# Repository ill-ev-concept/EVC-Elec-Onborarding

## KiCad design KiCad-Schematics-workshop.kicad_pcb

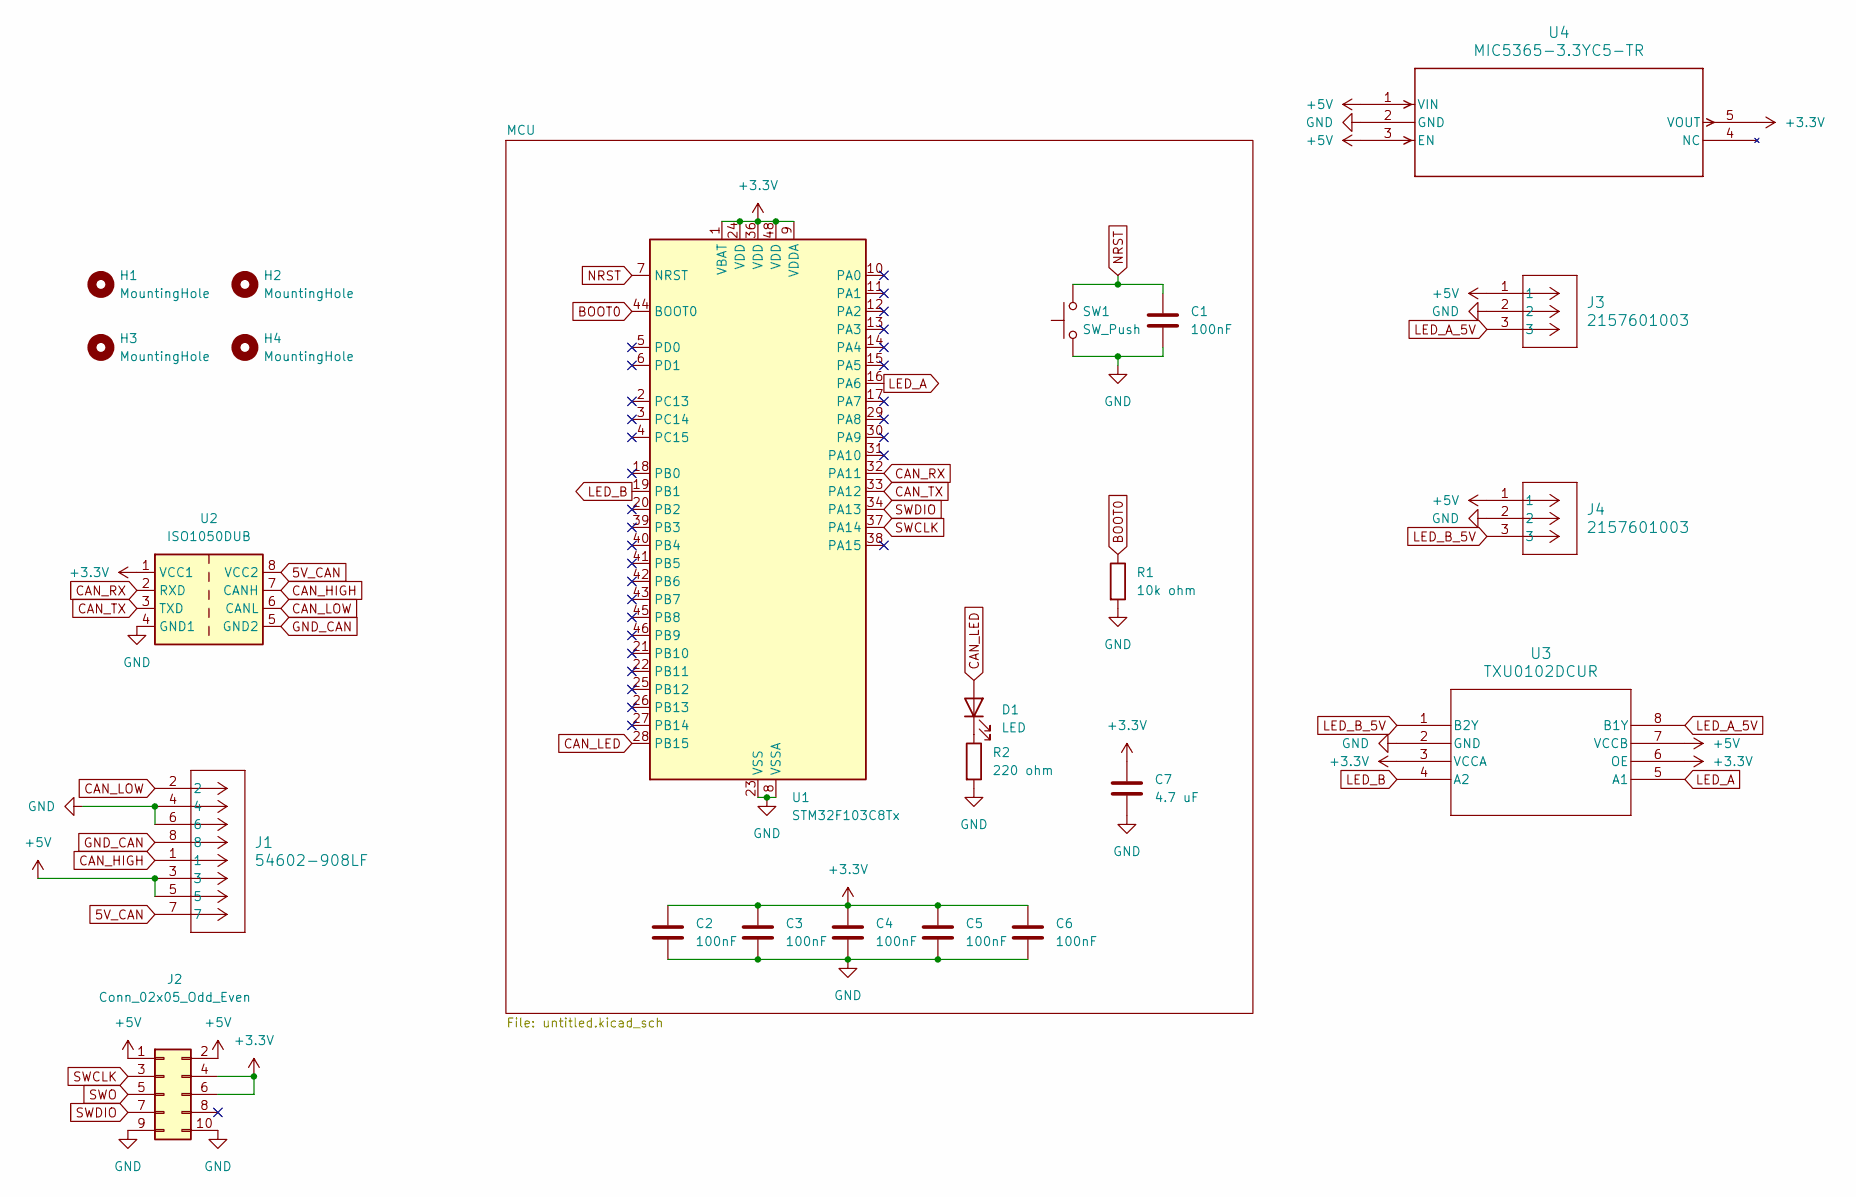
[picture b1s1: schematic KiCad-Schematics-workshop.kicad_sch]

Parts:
C1, C2, C3, C4, C5, C6: 100nF; C_0805_2012Metric
C7: 4.7 uF; C_0805_2012Metric
D1: LED; LED_0805_2012Metric
H1, H2, H3, H4: MountingHole; MountingHole_3.2mm_M3
J1: 54602-908LF; CONN8_2-908LF_AMP
J2: Conn_02x05_Odd_Even; PinHeader_2x05_P2.54mm_Horizontal
J3, J4: 2157601003; CONN_2157600003-SD_03_PEG_MOL
R1: 10k ohm; R_0805_2012Metric
R2: 220 ohm; R_0805_2012Metric
SW1: SW_Push; SW_SPST_EVQQ2
U1: STM32F103C8Tx; LQFP-48_7x7mm_P0.5mm
U2: ISO1050DUB; DUB0008A_L
U3: TXU0102DCUR; SOIC8_DCU_TEX
U4: MIC5365-3.3YC5-TR; SC-70_C5_MCH

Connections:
5V_CAN: J1.7, U2.8 (VCC2)
+3.3V: C2.1, C3.1, C4.1, C5.1, C6.1, C7.1, J2.4, J2.6, U1.1 (VBAT), U1.9 (VDDA), U1.24 (VDD), U1.36 (VDD), U1.48 (VDD), U2.1 (VCC1), U3.3 (VCCA), U3.6 (OE), U4.5 (VOUT)
+5V: J1.3, J1.5, J2.1, J2.2, J3.1, J4.1, U3.7 (VCCB), U4.1 (VIN), U4.3 (EN)
BOOT0: R1.1, U1.44 (BOOT0)
CAN_HIGH: J1.1, U2.7 (CANH)
CAN_LED: D1.2 (A), U1.28 (PB15)
CAN_LOW: J1.2, U2.6 (CANL)
CAN_RX: U1.32 (PA11), U2.2 (RXD)
CAN_TX: U1.33 (PA12), U2.3 (TXD)
GND: C1.2, C2.2, C3.2, C4.2, C5.2, C6.2, C7.2, J1.4, J1.6, J2.9, J2.10, J3.2, J4.2, R1.2, R2.2, SW1.1, U1.8 (VSSA), U1.23 (VSS), U1.35 (VSS), U1.47 (VSS), U2.4 (GND1), U3.2 (GND), U4.2 (GND)
GND_CAN: J1.8, U2.5 (GND2)
LED_A: U1.16 (PA6), U3.5 (A1)
LED_A_5V: J3.3, U3.8 (B1Y)
LED_B: U1.19 (PB1), U3.4 (A2)
LED_B_5V: J4.3, U3.1 (B2Y)
NRST: C1.1, SW1.2, U1.7 (NRST)
unnamed: D1.1 (K), R2.1
SWCLK: J2.3, U1.37 (PA14)
SWDIO: J2.7, U1.34 (PA13)
SWO: J2.5

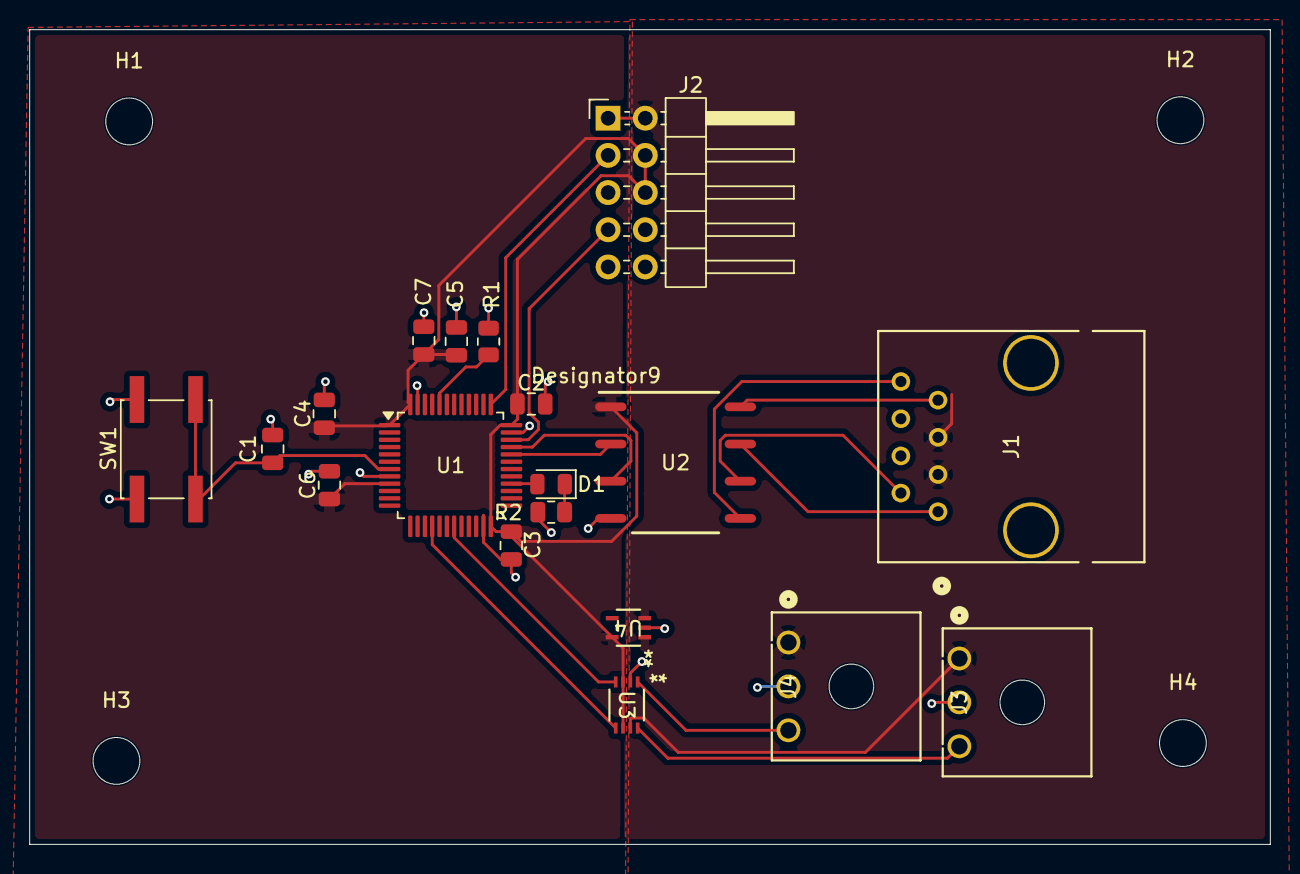
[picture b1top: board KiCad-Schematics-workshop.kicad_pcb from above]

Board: 2 copper layers, 84.8 x 55.7 mm, 23 parts (0 on the bottom side), 19 nets.

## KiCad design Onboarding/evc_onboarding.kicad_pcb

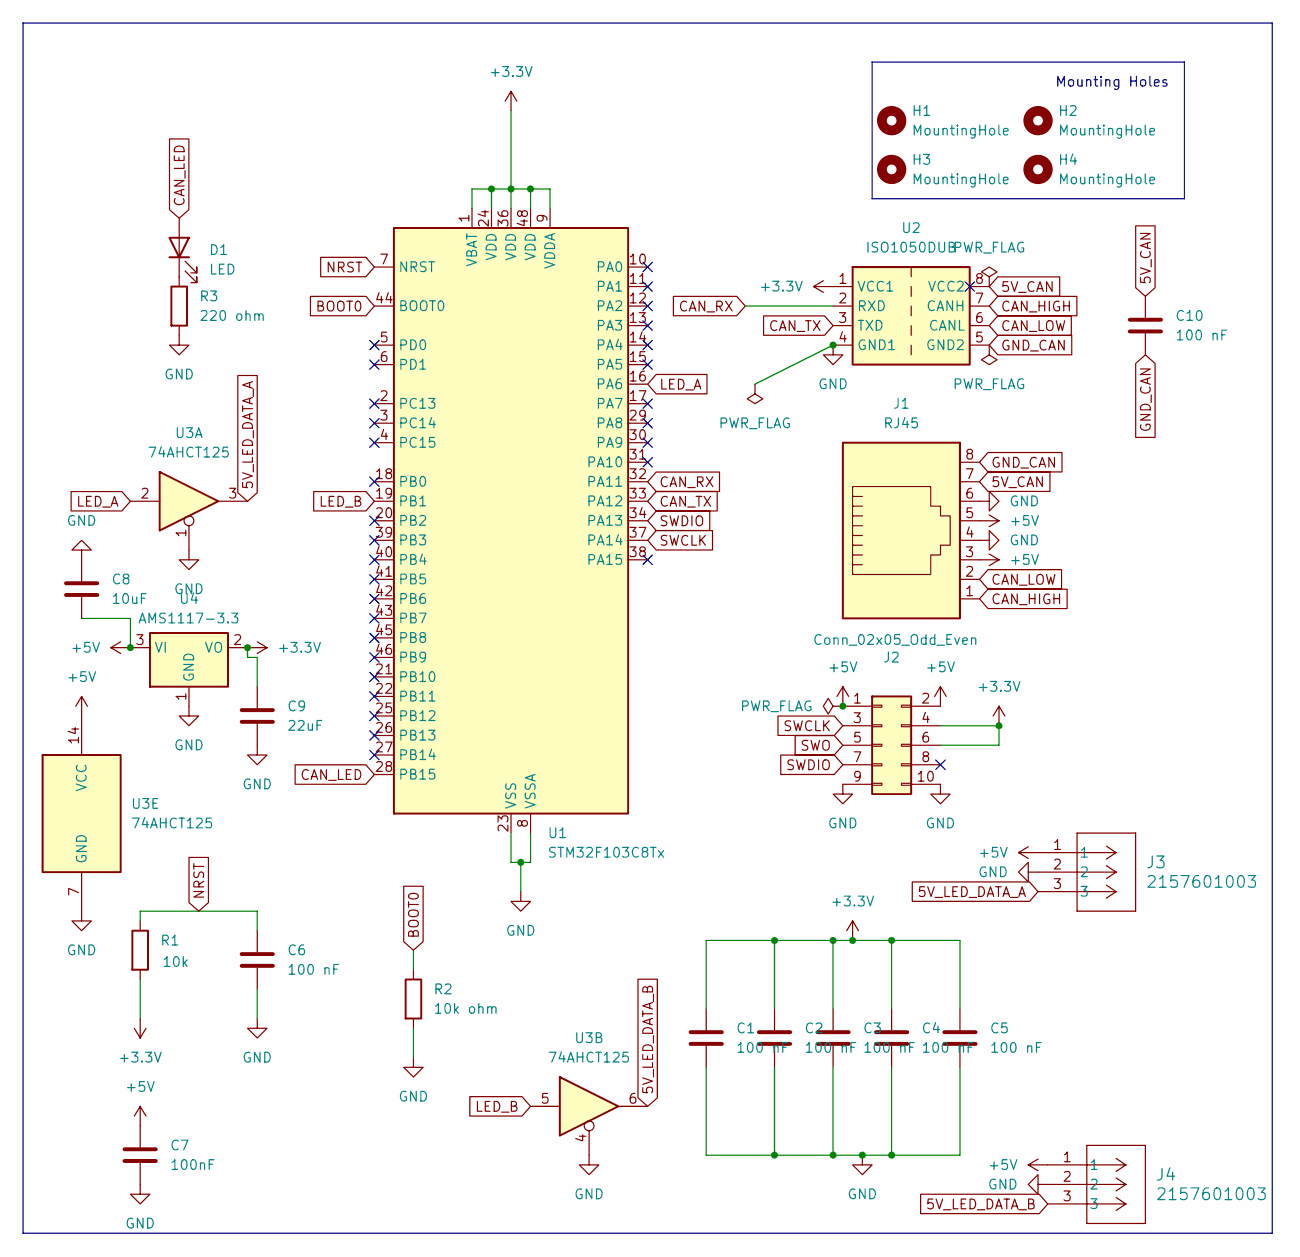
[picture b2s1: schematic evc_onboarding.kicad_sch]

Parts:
C1, C2, C3, C4, C5, C6, C10: 100 nF; C_0805_2012Metric
C7: 100nF; C_0805_2012Metric
C8: 10uF; C_1206_3216Metric
C9: 22uF; C_1206_3216Metric
D1: LED; LED_0805_2012Metric
H1, H2, H3, H4: MountingHole; MountingHole_4.3mm_M4
J1: RJ45; RJ45_Amphenol_RJMG1BD3B8K1ANR
J2: Conn_02x05_Odd_Even; PinHeader_2x05_P2.54mm_Vertical
J3, J4: 2157601003; CONN_2157600003-SD_03_PEG_MOL
R1: 10k; R_0805_2012Metric
R2: 10k ohm; R_0805_2012Metric
R3: 220 ohm; R_0805_2012Metric
U1: STM32F103C8Tx; LQFP-48_7x7mm_P0.5mm
U2: ISO1050DUB; SOP-8_6.62x9.15mm_P2.54mm
U3: 74AHCT125; SOIC-14_3.9x8.7mm_P1.27mm
U4: AMS1117-3.3; SOT-223-3_TabPin2

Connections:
5V_CAN: C10.1, J1.7, U2.8 (VCC2)
5V_LED_DATA_A: J3.3, U3.3
5V_LED_DATA_B: J4.3, U3.6
+3.3V: C1.1, C2.1, C3.1, C4.1, C5.1, C9.1, J2.4, J2.6, R1.2, U1.1 (VBAT), U1.9 (VDDA), U1.24 (VDD), U1.36 (VDD), U1.48 (VDD), U2.1 (VCC1), U4.2 (VO)
+5V: C7.1, C8.2, J1.3, J1.5, J2.1, J2.2, J3.1, J4.1, U3.14 (VCC), U4.3 (VI)
BOOT0: R2.1, U1.44 (BOOT0)
CAN_HIGH: J1.1, U2.7 (CANH)
CAN_LED: D1.2 (A), U1.28 (PB15)
CAN_LOW: J1.2, U2.6 (CANL)
CAN_RX: U1.32 (PA11), U2.2 (RXD)
CAN_TX: U1.33 (PA12), U2.3 (TXD)
GND: C1.2, C2.2, C3.2, C4.2, C5.2, C6.2, C7.2, C8.1, C9.2, J1.4, J1.6, J2.9, J2.10, J3.2, J4.2, R2.2, R3.2, U1.8 (VSSA), U1.23 (VSS), U1.35 (VSS), U1.47 (VSS), U2.4 (GND1), U3.1, U3.4, U3.7 (GND), U4.1 (GND)
GND_CAN: C10.2, J1.8, U2.5 (GND2)
LED_A: U1.16 (PA6), U3.2
LED_B: U1.19 (PB1), U3.5
NRST: C6.1, R1.1, U1.7 (NRST)
unnamed: D1.1 (K), R3.1
SWCLK: J2.3, U1.37 (PA14)
SWDIO: J2.7, U1.34 (PA13)
SWO: J2.5

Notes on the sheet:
Mounting Holes

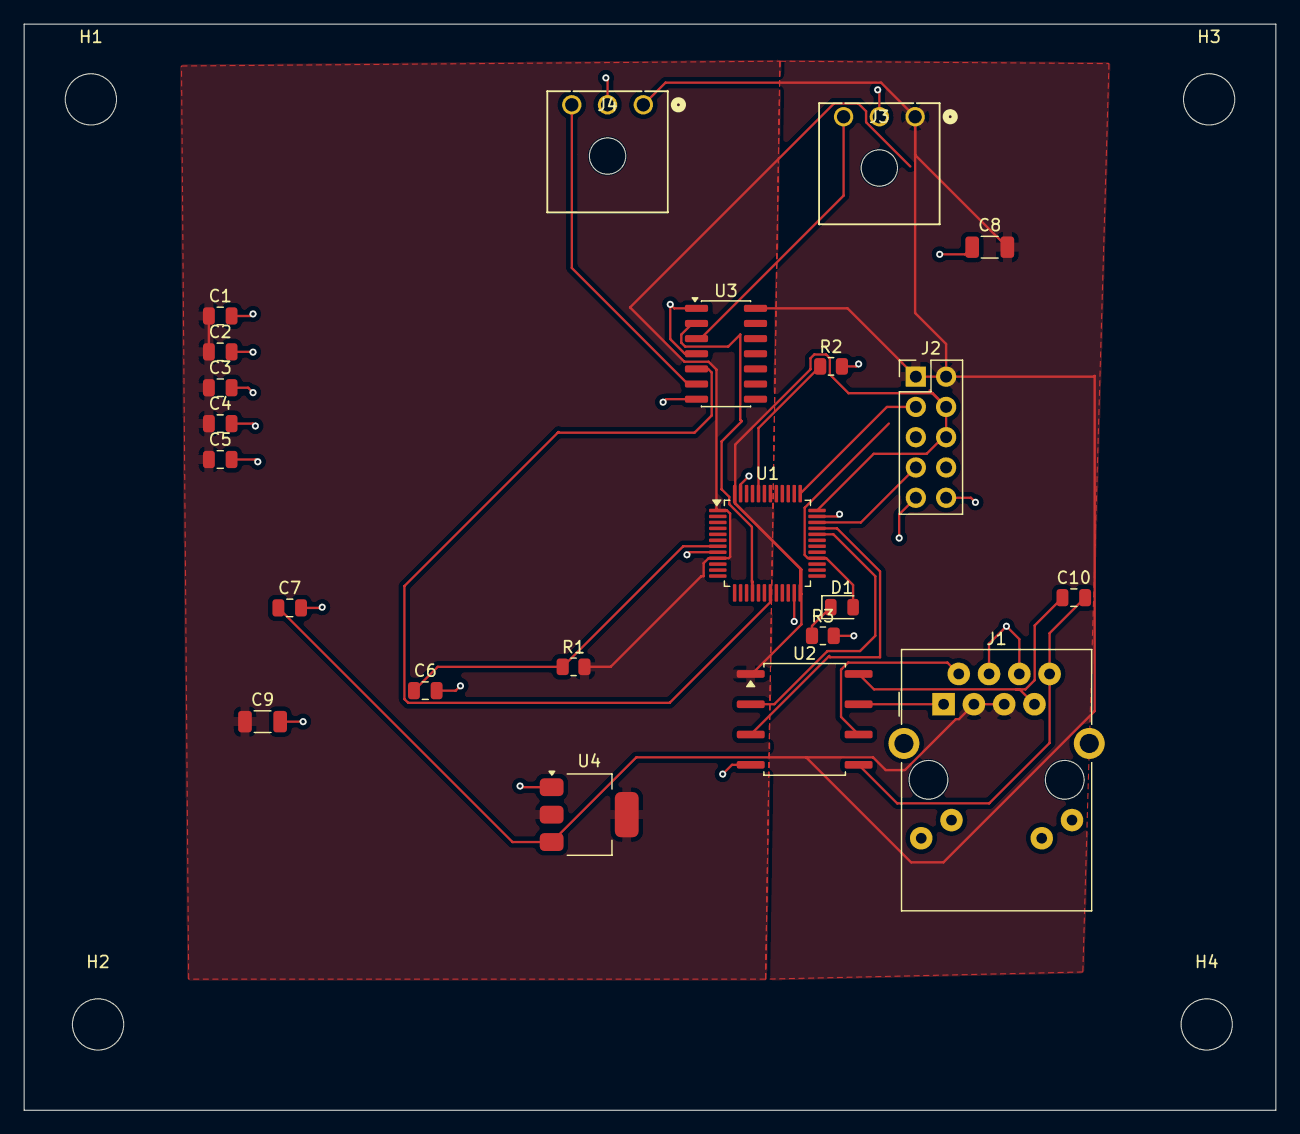
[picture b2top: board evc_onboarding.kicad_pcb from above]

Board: 2 copper layers, 105.0 x 91.1 mm, 26 parts (0 on the bottom side), 19 nets.

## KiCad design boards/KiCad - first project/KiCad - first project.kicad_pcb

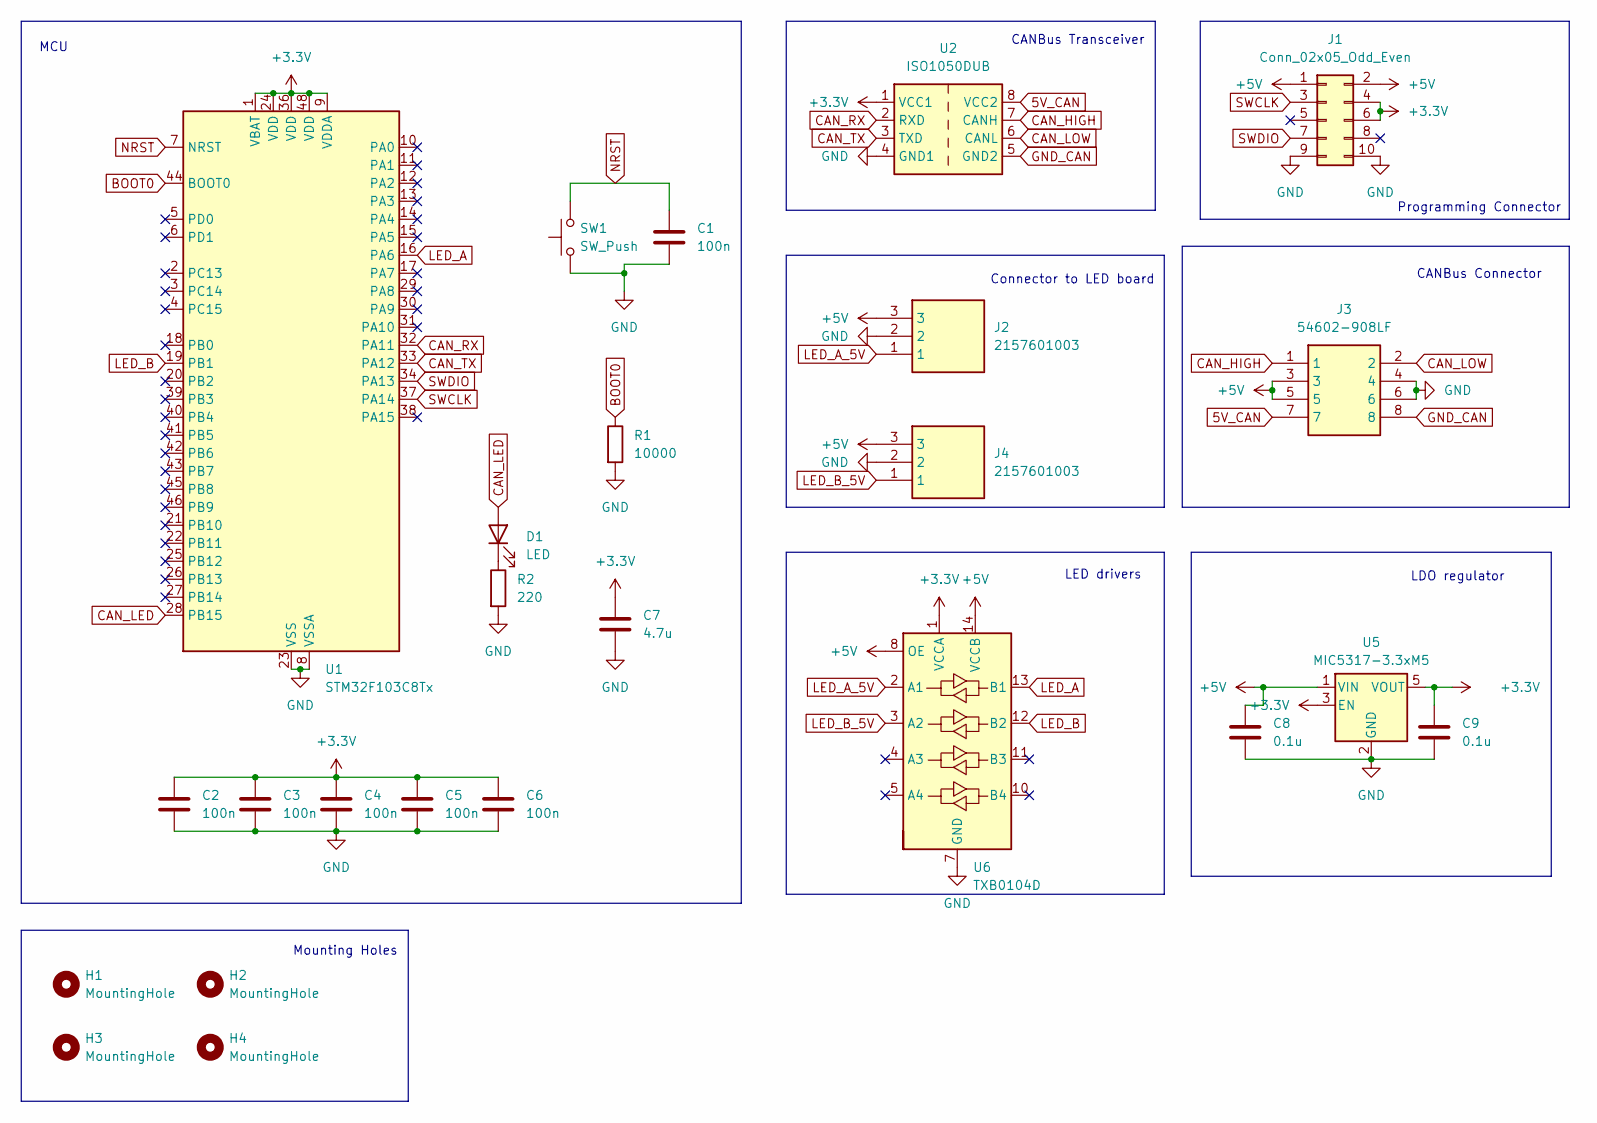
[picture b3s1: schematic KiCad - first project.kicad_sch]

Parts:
C1, C2, C3, C4, C5, C6: 100n; C_0805_2012Metric
C7: 4.7u; C_0805_2012Metric
C8, C9: 0.1u; C_0805_2012Metric
D1: LED; LED_0805_2012Metric
H1, H2, H3, H4: MountingHole; MountingHole_3.2mm_M3
J1: Conn_02x05_Odd_Even; PinSocket_2x05_P2.54mm_Vertical
J2, J4: 2157601003; 215760YY03; Manufacturer_Part_Number 2157601003
J3: 54602-908LF; 54602908LF; Manufacturer_Part_Number 54602-908LF
R1: 10000; R_0805_2012Metric
R2: 220; R_0805_2012Metric
SW1: SW_Push; SW_SPST_EVQQ2
U1: STM32F103C8Tx; LQFP-48_7x7mm_P0.5mm
U2: ISO1050DUB; SOP-8_6.62x9.15mm_P2.54mm
U5: MIC5317-3.3xM5; SOT-23-5
U6: TXB0104D; SOIC-14_3.9x8.7mm_P1.27mm

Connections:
5V_CAN: J3.7, U2.8 (VCC2)
+3.3V: C2.1, C3.1, C4.1, C5.1, C6.1, C7.1, C9.1, J1.4, J1.6, U1.1 (VBAT), U1.9 (VDDA), U1.24 (VDD), U1.36 (VDD), U1.48 (VDD), U2.1 (VCC1), U5.3 (EN), U5.5 (VOUT), U6.1 (VCCA)
+5V: C8.1, J1.1, J1.2, J2.3, J3.3, J3.5, J4.3, U5.1 (VIN), U6.8 (OE), U6.14 (VCCB)
BOOT0: R1.1, U1.44 (BOOT0)
CAN_HIGH: J3.1, U2.7 (CANH)
CAN_LED: D1.2 (A), U1.28 (PB15)
CAN_LOW: J3.2, U2.6 (CANL)
CAN_RX: U1.32 (PA11), U2.2 (RXD)
CAN_TX: U1.33 (PA12), U2.3 (TXD)
GND: C1.2, C2.2, C3.2, C4.2, C5.2, C6.2, C7.2, C8.2, C9.2, J1.9, J1.10, J2.2, J3.4, J3.6, J4.2, R1.2, R2.2, SW1.1, U1.8 (VSSA), U1.23 (VSS), U1.35 (VSS), U1.47 (VSS), U2.4 (GND1), U5.2 (GND), U6.7 (GND)
GND_CAN: J3.8, U2.5 (GND2)
LED_A: U1.16 (PA6), U6.13 (B1)
LED_A_5V: J2.1, U6.2 (A1)
LED_B: U1.19 (PB1), U6.12 (B2)
LED_B_5V: J4.1, U6.3 (A2)
NRST: C1.1, SW1.2, U1.7 (NRST)
unnamed: D1.1 (K), R2.1
SWCLK: J1.3, U1.37 (PA14)
SWDIO: J1.7, U1.34 (PA13)

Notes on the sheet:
LED drivers
Connector to LED board
MCU
Mounting Holes
LDO regulator
CANBus Transceiver
Programming Connector
CANBus Connector

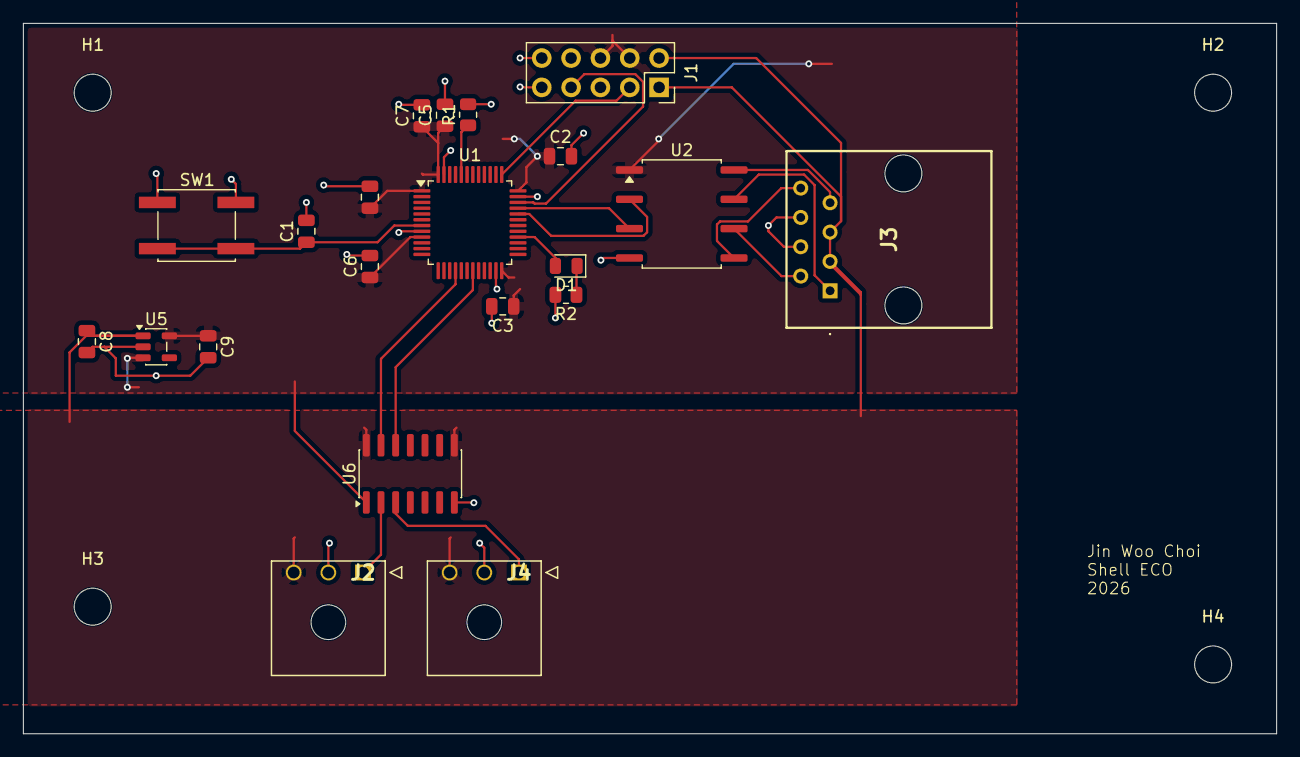
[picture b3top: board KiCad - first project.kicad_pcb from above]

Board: 2 copper layers, 108.5 x 61.5 mm, 25 parts (0 on the bottom side), 19 nets.

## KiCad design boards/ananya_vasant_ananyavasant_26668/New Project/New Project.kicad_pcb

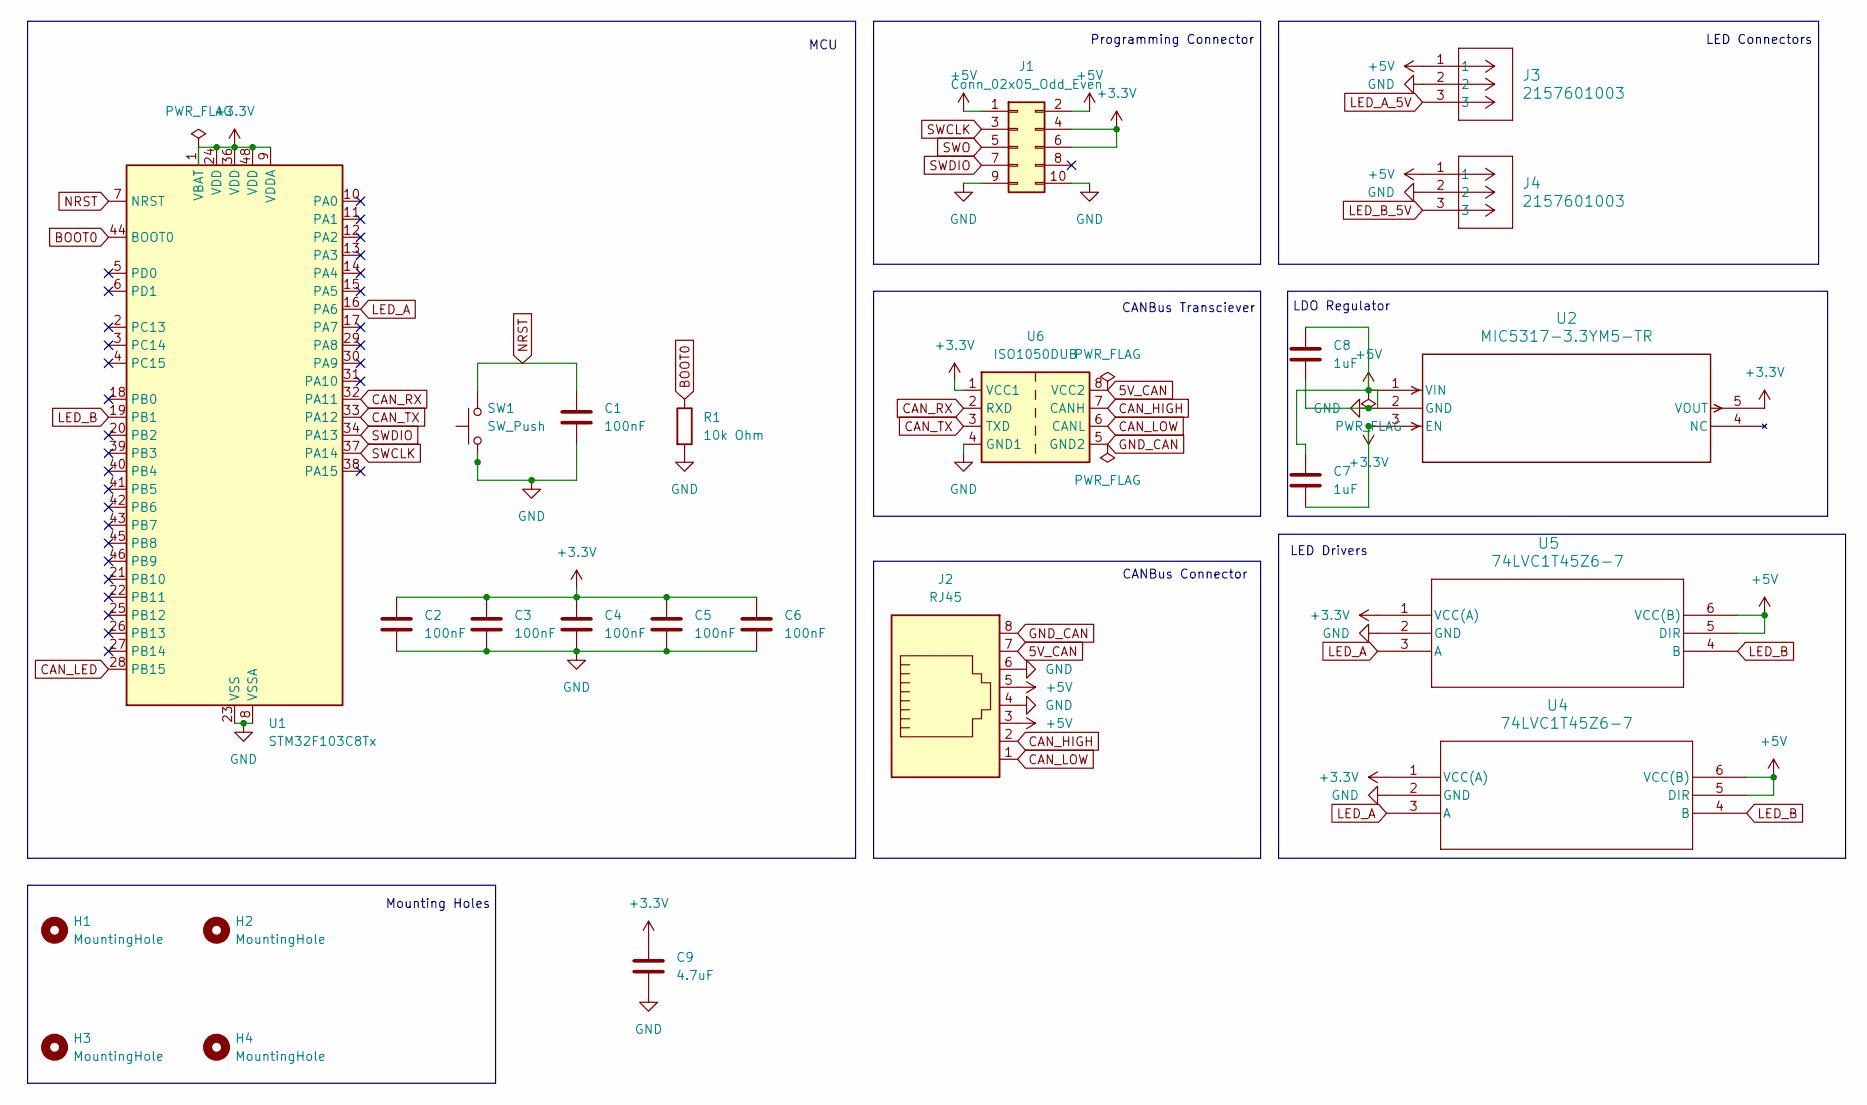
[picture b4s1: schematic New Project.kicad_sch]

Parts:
C1, C2, C3, C4, C5, C6: 100nF; C_0805_2012Metric
C7, C8: 1uF; C_0805_2012Metric
C9: 4.7uF; C_0805_2012Metric
H1, H2, H3, H4: MountingHole; MountingHole_3.2mm_M3
J1: Conn_02x05_Odd_Even; PinHeader_2x05_P2.54mm_Vertical
J2: RJ45; CONN8_2-908LF_AMP
J3, J4: 2157601003; CONN_2157600003-SD_03_PEG_MOL
R1: 10k Ohm; R_0805_2012Metric
SW1: SW_Push; SW_SPST_EVQQ2
U1: STM32F103C8Tx; LQFP-48_7x7mm_P0.5mm
U2: MIC5317-3.3YM5-TR; SOT-23-5_M5_MCH
U4, U5: 74LVC1T45Z6-7; SOT-563_DIO
U6: ISO1050DUB; DUB0008A_N

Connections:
5V_CAN: J2.7, U6.8 (VCC2)
+3.3V: C2.1, C3.1, C4.1, C5.1, C6.1, C7.2, C9.1, J1.4, J1.6, U1.1 (VBAT), U1.9 (VDDA), U1.24 (VDD), U1.36 (VDD), U1.48 (VDD), U2.3 (EN), U2.5 (VOUT), U4.1 (VCC(A)), U5.1 (VCC(A)), U6.1 (VCC1)
+5V: C7.1, C8.1, J1.1, J1.2, J2.3, J2.5, J3.1, J4.1, U2.1 (VIN), U4.5 (DIR), U4.6 (VCC(B)), U5.5 (DIR), U5.6 (VCC(B))
BOOT0: R1.1, U1.44 (BOOT0)
CAN_HIGH: J2.2, U6.7 (CANH)
CAN_LED: U1.28 (PB15)
CAN_LOW: J2.1, U6.6 (CANL)
CAN_RX: U1.32 (PA11), U6.2 (RXD)
CAN_TX: U1.33 (PA12), U6.3 (TXD)
GND: C1.2, C2.2, C3.2, C4.2, C5.2, C6.2, C8.2, C9.2, J1.9, J1.10, J2.4, J2.6, J3.2, J4.2, R1.2, SW1.1, U1.8 (VSSA), U1.23 (VSS), U1.35 (VSS), U1.47 (VSS), U2.2 (GND), U4.2 (GND), U5.2 (GND), U6.4 (GND1)
GND_CAN: J2.8, U6.5 (GND2)
LED_A: U1.16 (PA6), U4.3 (A), U5.3 (A)
LED_A_5V: J3.3
LED_B: U1.19 (PB1), U4.4 (B), U5.4 (B)
LED_B_5V: J4.3
NRST: C1.1, SW1.2, U1.7 (NRST)
SWCLK: J1.3, U1.37 (PA14)
SWDIO: J1.7, U1.34 (PA13)
SWO: J1.5

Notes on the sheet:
LED Drivers
CANBus Transciever
CANBus Connector
Programming Connector
LDO Regulator
LED Connectors
Mounting Holes
MCU

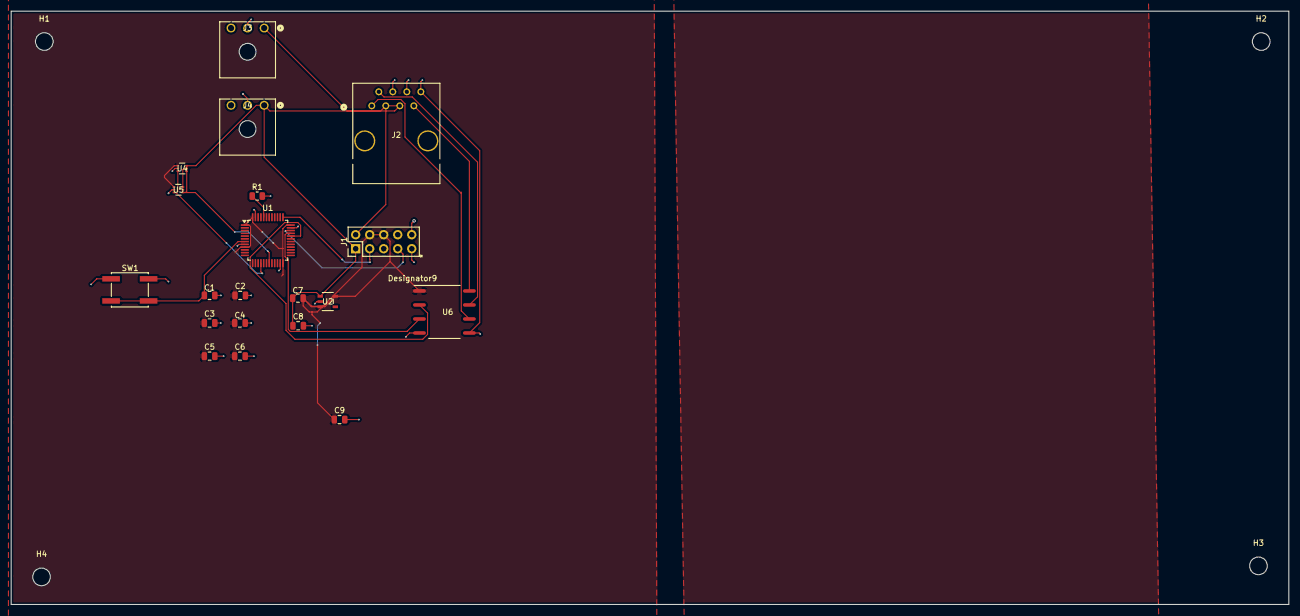
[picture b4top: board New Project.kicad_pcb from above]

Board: 2 copper layers, 231.5 x 107.5 mm, 24 parts (0 on the bottom side), 15 nets.
